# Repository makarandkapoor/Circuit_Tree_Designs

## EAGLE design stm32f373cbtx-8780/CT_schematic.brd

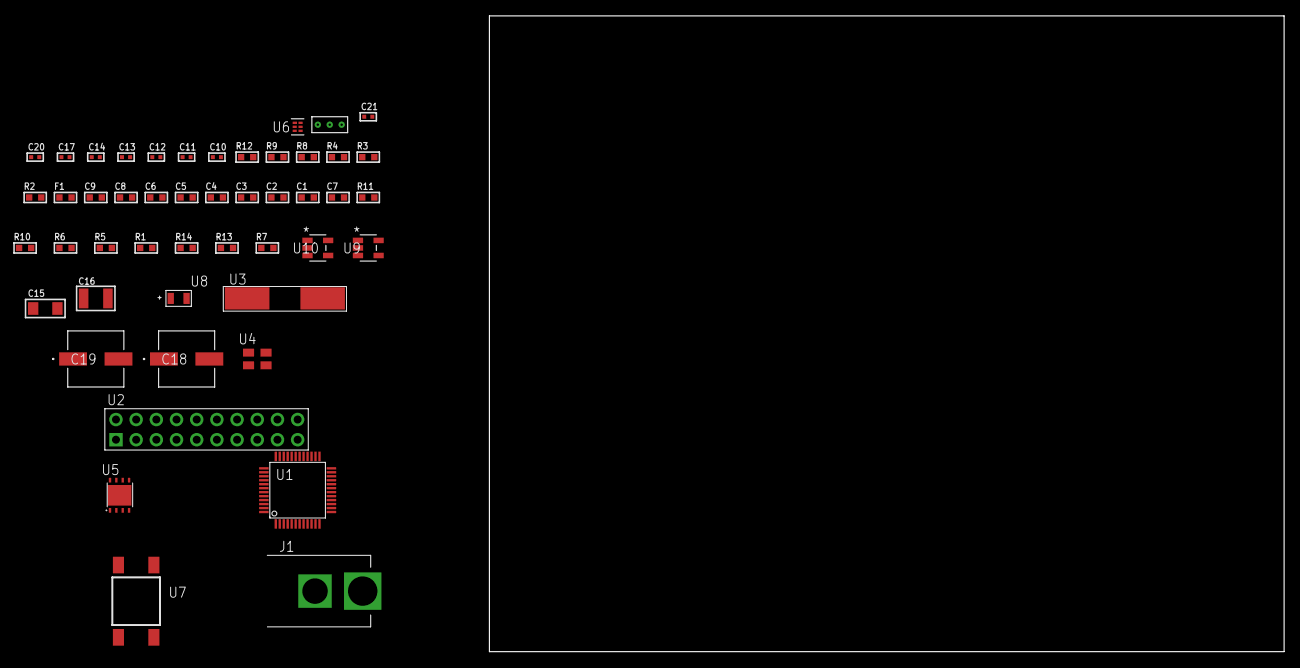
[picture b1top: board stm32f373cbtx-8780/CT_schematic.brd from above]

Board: 2 copper layers, 100.0 x 80.0 mm, 48 parts (0 on the bottom side), 24 nets, no tracks yet.

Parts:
C1, C9: 1e-06; C0603
C2, C3, C4, C5, C6: 1e-07; C0603
C7: 4.7e-06; C0603
C8: 1e-08; C0603
C10, C11: 1e-11; C0402
C12, C17: 1e-07; C0402
C13, C14, C20, C21: 1e-08; C0402
C15: 1e-05; C1206
C16: 1e-05; C1210
C18, C19: 0.0001; EXV-9H
F1: 240.0; L0603
J1: PJ-037B; PJ-037B_PACKAGE
R1, R5, R6, R10, R11: 10000.0; R0603
R2, R9: 1000.0; R0603
R3: 1600.5; R0603
R4: 4700.0; R0603
R7: 100000.0; R0603
R8: 2231.0; R0603
R12: 9100.0; R0603
R13: 680000.0; R0603
R14: 120000.0; R0603
U1: STM32F373CBT7; LQFP48
U2: TST-110-05-T-D-RA
U3: ABLS-25.000MHZ-B2F-T
U4: ASEK-32.768KHz-ECST; ASEK
U5: LP3878SDX-ADJ/NOPB; WSON-8
U6: TPS3895ADRYR; SON-6
U7: 4-1437565-2; SW_4-1437565-2
U8: Q65110A2395; LGM67K-G1J2-24-Z
U9, U10: nc7sz125m5x; NC7SZ125M5X
U11: Dummy; DUMMY_PACKAGE_98

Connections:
CLK_CRYSTAL_U1_5: C10.1, U1.5, U3.1
CLK_CRYSTAL_U1_6: C11.1, U1.6, U3.2
CLK_U1_3: U1.3, U4.3
GND: C1.2, C2.2, C3.2, C4.2, C5.2, C6.2, C7.2, C8.2, C9.2, C10.2, C11.2, C12.2, C13.2, C14.2, C15.2, C16.2, C17.2, C18.2, C19.2, C20.2, C21.2, J1.2, R2.2, R5.2, R9.2, R12.2, R14.2, U1.8, U1.23, U1.47, U2.4, U2.6, U2.8, U2.10, U2.12, U2.14, U2.16, U2.18, U2.20, U4.2, U5.3, U5.PAD, U6.2, U8.C, U9.2, U9.3, U10.1, U10.3, U11.1
NET_U1_7: R4.1, U1.7, U10.4
NET_U1_9: C8.1, C9.1, F1.1, U1.9, U1.24, U1.25
NET_U1_44: R5.1, U1.44
NET_U1_45: R3.1, U1.45, U8.A
NET_U1_46: R1.1, U1.46, U7.3, U7.4
NET_U5_1: C14.1, U5.1
NET_U5_6: R8.2, R9.1, U5.6
NET_U5_8: R7.1, U5.8
NET_U6_1: R11.1, R12.1, U6.1
NET_U6_3: R13.2, R14.1, U6.3
NET_U6_4: R10.1, U6.4, U9.4, U10.2
NET_U7_1: R2.1, U7.1, U7.2
PROC_SYS_JTCK_SWCLK: U1.37, U2.9
PROC_SYS_JTDO_TRACESWO: U1.39, U2.13
PROC_SYS_JTMS_SWDIO: U1.34, U2.7
PROC_TIM12_CH1: U1.14, U11.3
PROC_TIM12_CH2: U1.15, U11.2
RST_OUT_U2_SRESET_B: R6.1, U2.15, U9.1
VCC_S1_5V9: C15.1, C18.1, C19.1, J1.1, R7.2, U5.4
VCC_TIER1_3V3: C1.1, C2.1, C3.1, C4.1, C5.1, C6.1, C7.1, C12.1, C13.1, C16.1, C17.1, C20.1, C21.1, F1.2, R1.2, R3.2, R4.2, R6.2, R8.1, R10.2, R11.2, R13.1, U1.1, U1.17, U1.48, U2.1, U4.4, U5.5, U6.6, U9.5, U10.5

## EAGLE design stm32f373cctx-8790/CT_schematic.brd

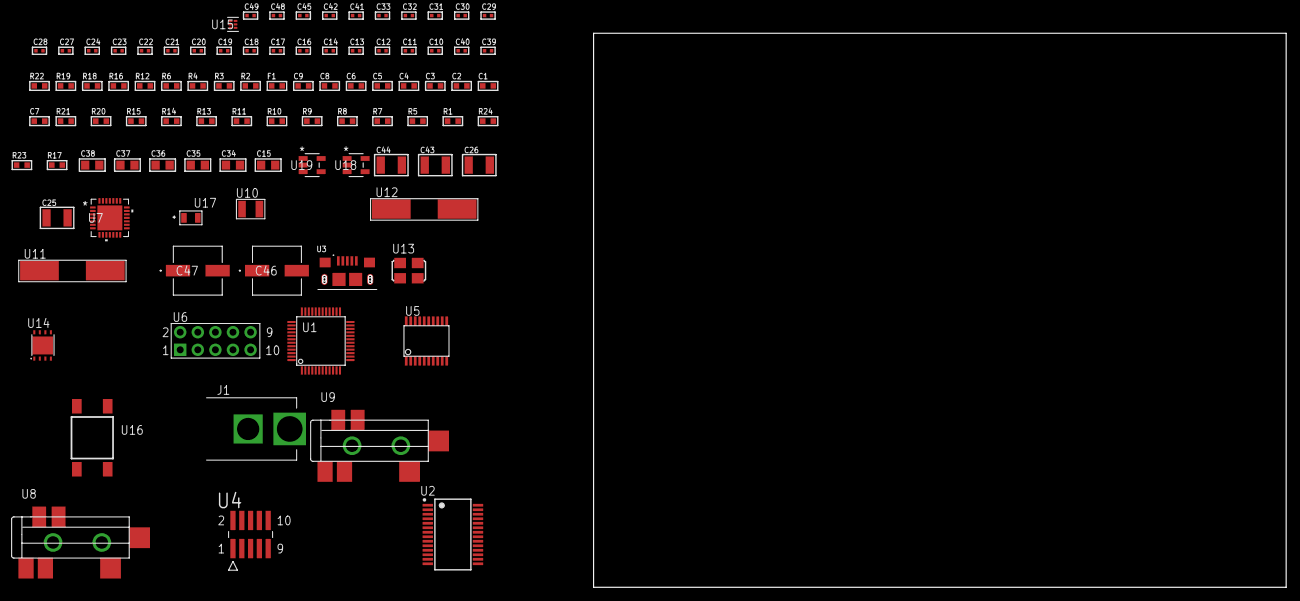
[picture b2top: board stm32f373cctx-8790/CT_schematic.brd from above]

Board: 2 copper layers, 94 parts (0 on the bottom side), 58 nets, no tracks yet.

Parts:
C1, C9: 1e-06; C0603
C2, C3, C4, C5, C6: 1e-07; C0603
C7: 4.7e-06; C0603
C8: 1e-08; C0603
C10, C11, C12, C13: 1e-11; C0402
C14, C16, C17, C18, C19, C20, C21, C22, C23, C24, C29, C30, C31, C32, C33, C45: 1e-07; C0402
C15: 4.7e-06; C0805
C25, C26: 2.2e-05; C1210
C27, C28: 1e-09; C0402
C34, C35, C36, C37, C38: 1e-05; C0805
C39, C40: 2.2e-11; C0402
C41, C42, C48, C49: 1e-08; C0402
C43, C44: 1e-05; C1210
C46, C47: 0.0001; EXV-9H
F1: 240.0; L0603
J1: PJ-037B; PJ-037B_PACKAGE
R1, R5, R7, R8, R9, R10, R11, R20, R21: 10000.0; R0603
R2, R19: 1000.0; R0603
R3: 1600.5; R0603
R4, R6: 4700.0; R0603
R12: 5.0; R0603
R13, R14, R15: 47000.0; R0603
R16: 680.0; R0603
R17: 100000.0; R0603
R18: 2231.0; R0603
R22: 9100.0; R0603
R23: 680000.0; R0603
R24: 120000.0; R0603
U1: STM32F373CCT6; LQFP48
U2: FT232RL-REEL; SSOP-28
U3: 10118193-0001LF; FCI_10118193-0001LF
U4: FTSH-105-01-L-DV-K; SAMTEC_FTSH-105-01-L-DV-K
U5: SP3203ECY-L/TR; TSSOP20-I
U6: HTSS-105-01-G-D
U7: WM8731CLSEFL; QFN-28
U8, U9: SJ-43515TS-SMT-TR
U10: ABS07-32.768KHZ-7-T
U11: ABLS-25.000MHZ-B2F-T
U12: ABLS-12.288MHZ-B4-T
U13: ASFL1-12MHZ-NCS; ASFL1
U14: LP3878SDX-ADJ/NOPB; WSON-8
U15: TPS3895ADRYR; SON-6
U16: 4-1437565-2; SW_4-1437565-2
U17: Q65110A2395; LGM67K-G1J2-24-Z
U18, U19: nc7sz125m5x; NC7SZ125M5X

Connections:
CLK_CRYSTAL_U1_3: C10.1, U1.3, U10.1
CLK_CRYSTAL_U1_4: C11.1, U1.4, U10.2
CLK_CRYSTAL_U1_5: C12.1, U1.5, U11.1
CLK_CRYSTAL_U1_6: C13.1, U1.6, U11.2
CLK_CRYSTAL_U7_1: C39.1, U7.1, U12.1
CLK_CRYSTAL_U7_2: C40.1, U7.2, U12.2
CLK_U2_27: U2.27, U13.3
GND: C1.2, C2.2, C3.2, C4.2, C5.2, C6.2, C7.2, C8.2, C9.2, C10.2, C11.2, C12.2, C13.2, C14.2, C15.2, C16.2, C17.2, C18.2, C19.2, C20.2, C23.2, C24.2, C28.2, C29.2, C30.2, C31.2, C32.2, C33.2, C34.2, C35.2, C36.2, C37.2, C38.2, C39.2, C40.2, C41.2, C42.2, C43.2, C44.2, C45.2, C46.2, C47.2, C48.2, C49.2, J1.2, R2.2, R5.2, R8.2, R12.2, R13.2, R14.2, R15.2, R19.2, R22.2, R24.2, U1.8, U1.23, U1.47, U2.7, U2.18, U2.21, U2.25, U2.26, U3.5, U3.6, U3.7, U3.8, U3.9, U4.3, U4.5, U5.18, U6.9, U7.4, U7.15, U7.19, U7.25, U7.26, U7.29, U8.1, U9.1, U13.2, U14.3, U14.PAD, U15.2, U17.C, U18.2, U18.3, U19.1, U19.3
NET_U1_7: R4.1, U1.7, U19.4
NET_U1_9: C8.1, C9.1, F1.1, U1.9, U1.24, U1.25
NET_U1_44: R5.1, U1.44
NET_U1_45: R3.1, U1.45, U17.A
NET_U1_46: R1.1, U1.46, U16.3, U16.4
NET_U2_14: R7.1, U2.14
NET_U2_17: C16.1, U2.17
NET_U2_19: R8.1, U2.19
NET_U3_1: R6.1, U3.1
NET_U3_2: U2.16, U3.2
NET_U3_3: U2.15, U3.3
NET_U4_9: R12.1, U4.9
NET_U5_1: C21.1, U5.1
NET_U5_2: C23.1, U5.2
NET_U5_3: C21.2, U5.3
NET_U5_4: C22.1, U5.4
NET_U5_5: C22.2, U5.5
NET_U5_6: C24.1, U5.6
NET_U6_3: U5.14, U6.3
NET_U6_4: U5.13, U6.4
NET_U6_5: U5.17, U6.5
NET_U6_6: U5.16, U6.6
NET_U7_20: C33.1, C38.1, U7.20
NET_U8_2: C26.1, R14.1, U8.2
NET_U8_5: C25.1, R13.1, U8.5
NET_U9_5: C27.1, C28.1, R15.1, R16.1, U9.5
NET_U14_1: C42.1, U14.1
NET_U14_6: R18.2, R19.1, U14.6
NET_U14_8: R17.1, U14.8
NET_U15_1: R21.1, R22.1, U15.1
NET_U15_3: R23.2, R24.1, U15.3
NET_U15_4: R20.1, U15.4, U18.4, U19.2
NET_U16_1: R2.1, U16.1, U16.2
PROC_I2S1_CK: U1.15, U7.7
PROC_I2S1_SD: U1.18, U7.8
PROC_I2S1_WS: U1.14, U7.9, U7.11
PROC_SYS_JTCK_SWCLK: R10.1, U1.37, U4.4
PROC_SYS_JTDO_TRACESWO: U1.39, U4.6
PROC_SYS_JTMS_SWDIO: R11.1, U1.34, U4.2
PROC_USART1_CTS: U1.32, U5.8
PROC_USART1_RTS: U1.33, U5.10
PROC_USART1_RX: U1.31, U5.11
PROC_USART1_TX: U1.30, U5.7
PROC_USART2_CTS: U1.10, U2.3
PROC_USART2_RTS: U1.11, U2.11
PROC_USART2_RX: U1.13, U2.1
PROC_USART2_TX: U1.12, U2.5
RST_OUT_U4_JTAG_RST_B: R9.1, U4.10, U18.1
VCC_S1_12V7: C43.1, C46.1, C47.1, J1.1, R17.2, U14.4
VCC_TIER1_3V3: C1.1, C2.1, C3.1, C4.1, C5.1, C6.1, C7.1, C14.1, C15.1, C17.1, C18.1, C19.1, C20.1, C29.1, C30.1, C31.1, C32.1, C34.1, C35.1, C36.1, C37.1, C41.1, C44.1, C45.1, C48.1, C49.1, F1.2, R1.2, R3.2, R4.2, R7.2, R9.2, R10.2, R11.2, R18.1, R20.2, R21.2, R23.1, U1.1, U1.17, U1.48, U2.4, U2.20, U4.1, U5.12, U5.19, U7.3, U7.5, U7.12, U7.18, U13.4, U14.5, U15.6, U18.5, U19.5

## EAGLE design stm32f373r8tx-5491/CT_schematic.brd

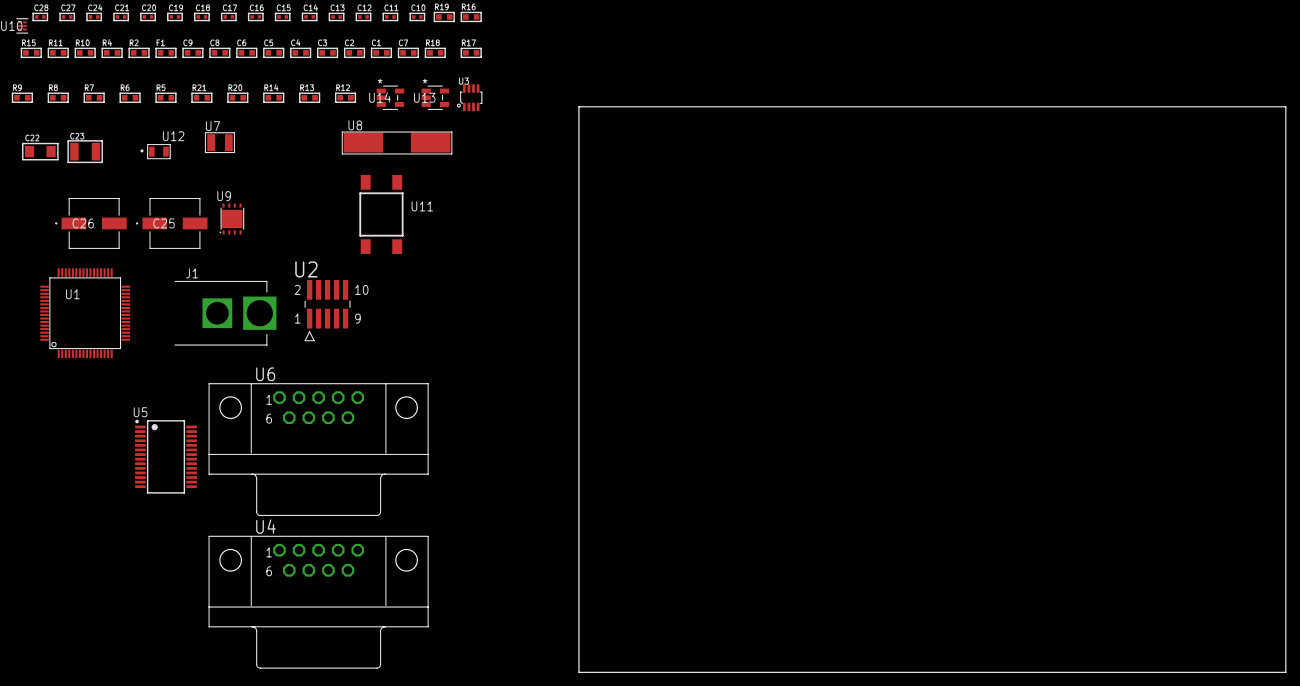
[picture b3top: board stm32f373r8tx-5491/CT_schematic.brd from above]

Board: 2 copper layers, 100.0 x 80.0 mm, 63 parts (0 on the bottom side), 45 nets, no tracks yet.

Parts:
C1, C9: 1e-06; C0603
C2, C3, C4, C5, C6: 1e-07; C0603
C7: 4.7e-06; C0603
C8: 1e-08; C0603
C10, C11, C12, C13: 1e-11; C0402
C14, C15, C16, C17, C18, C19, C20, C24: 1e-07; C0402
C21, C27, C28: 1e-08; C0402
C22: 1e-05; C1206
C23: 1e-05; C1210
C25, C26: 0.0001; EXV-9H
F1: 240.0; L0603
J1: PJ-037B; PJ-037B_PACKAGE
R2, R16: 1000.0; R0603
R4: 4700.0; R0603
R5, R6, R7, R8, R9, R17, R18: 10000.0; R0603
R10: 5.0; R0603
R11: 120.0; R0603
R12, R13, R14: 100000.0; R0603
R15: 2231.0; R0603
R19: 9100.0; R0603
R20: 680000.0; R0603
R21: 120000.0; R0603
U1: STM32F373R8T6; LQFP64
U2: FTSH-105-01-L-DV-K; SAMTEC_FTSH-105-01-L-DV-K
U3: MAX3051EKA+T; SOT-23-8
U4, U6: 182-009-113R531; 182-009-MALE
U5: ST3241EBPR; SSOP-28
U7: ABS07-32.768KHZ-7-T
U8: ABLS-25.000MHZ-B2F-T
U9: LP3878SDX-ADJ/NOPB; WSON-8
U10: TPS3895ADRYR; SON-6
U11: 4-1437565-2; SW_4-1437565-2
U12: Q65110A2395; LGM67K-G1J2-24-Z
U13, U14: nc7sz125m5x; NC7SZ125M5X

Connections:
CLK_CRYSTAL_U1_3: C10.1, U1.3, U7.1
CLK_CRYSTAL_U1_4: C11.1, U1.4, U7.2
CLK_CRYSTAL_U1_5: C12.1, U1.5, U8.1
CLK_CRYSTAL_U1_6: C13.1, U1.6, U8.2
GND: C1.2, C2.2, C3.2, C4.2, C5.2, C6.2, C7.2, C8.2, C9.2, C10.2, C11.2, C12.2, C13.2, C14.2, C15.2, C16.2, C19.2, C20.2, C21.2, C22.2, C23.2, C24.2, C25.2, C26.2, C27.2, C28.2, J1.2, R2.2, R5.2, R9.2, R10.2, R12.2, R16.2, R19.2, R21.2, U1.12, U1.31, U1.63, U2.3, U2.5, U3.2, U4.5, U5.23, U5.25, U6.5, U9.3, U9.PAD, U10.2, U12.C, U13.2, U13.3, U14.1, U14.3
NET_U1_7: R4.1, U1.7, U14.4
NET_U1_13: C8.1, C9.1, F1.1, U1.13, U1.17, U1.32
NET_U1_59: U11.3, U11.4
NET_U1_60: R5.1, U1.60
NET_U2_9: R10.1, U2.9
NET_U3_6: R11.2, U3.6
NET_U3_8: R12.1, U3.8
NET_U4_2: R11.2, U3.6, U4.2
NET_U4_3: R11.1, U3.7, U4.3
NET_U5_1: C18.1, U5.1
NET_U5_2: C18.2, U5.2
NET_U5_3: C20.1, U5.3
NET_U5_22: R13.1, U5.22
NET_U5_24: C17.2, U5.24
NET_U5_27: C19.1, U5.27
NET_U5_28: C17.1, U5.28
NET_U6_2: U5.4, U6.2
NET_U6_3: U5.9, U6.3
NET_U6_7: U5.5, U6.7
NET_U6_8: U5.10, U6.8
NET_U9_1: C21.1, U9.1
NET_U9_6: R15.2, R16.1, U9.6
NET_U9_8: R14.1, U9.8
NET_U10_1: R18.1, R19.1, U10.1
NET_U10_3: R20.2, R21.1, U10.3
NET_U10_4: R17.1, U10.4, U13.4, U14.2
NET_U11_1: R2.1, U11.1, U11.2
PROC_CAN_RX: U1.61, U3.4
PROC_CAN_TX: U1.62, U3.1
PROC_SYS_JTCK_SWCLK: R9.1, U1.49, U2.4
PROC_SYS_JTDI: R7.1, U1.50, U2.8
PROC_SYS_JTDO_TRACESWO: U1.55, U2.6
PROC_SYS_JTMS_SWDIO: R8.1, U1.46, U2.2
PROC_USART1_CTS: U1.44, U5.13
PROC_USART1_RTS: U1.45, U5.18
PROC_USART1_RX: U1.25, U5.19
PROC_USART1_TX: U1.24, U5.14
RST_OUT_U2_JTAG_RST_B: R6.1, U2.10, U13.1
VCC_S1_10V7: C22.1, C25.1, C26.1, J1.1, R14.2, U9.4
VCC_TIER1_3V3: C1.1, C2.1, C3.1, C4.1, C5.1, C6.1, C7.1, C14.1, C15.1, C16.1, C23.1, C24.1, C27.1, C28.1, F1.2, R4.2, R6.2, R7.2, R8.2, R13.2, R15.1, R17.2, R18.2, R20.1, U1.1, U1.19, U1.64, U2.1, U3.3, U5.26, U9.5, U10.6, U13.5, U14.5

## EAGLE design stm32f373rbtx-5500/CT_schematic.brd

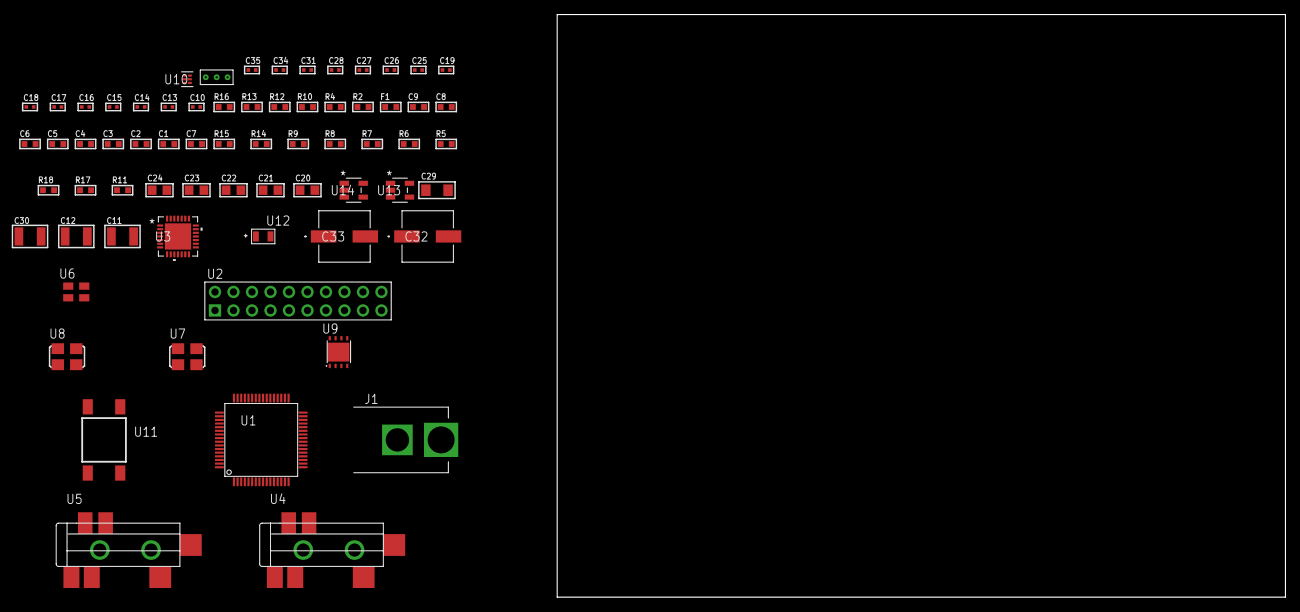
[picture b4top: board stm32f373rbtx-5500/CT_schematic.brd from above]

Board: 2 copper layers, 100.0 x 80.0 mm, 68 parts (0 on the bottom side), 30 nets, no tracks yet.

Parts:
C1, C9: 1e-06; C0603
C2, C3, C4, C5, C6: 1e-07; C0603
C7: 4.7e-06; C0603
C8: 1e-08; C0603
C10, C15, C16, C17, C18, C19, C31: 1e-07; C0402
C11, C12: 2.2e-05; C1210
C13, C14: 1e-09; C0402
C20, C21, C22, C23, C24: 1e-05; C0805
C25, C26, C27, C28, C34, C35: 1e-08; C0402
C29: 1e-05; C1206
C30: 1e-05; C1210
C32, C33: 0.0001; EXV-9H
F1: 240.0; L0603
J1: PJ-037B; PJ-037B_PACKAGE
R2, R13: 1000.0; R0603
R4: 4700.0; R0603
R5, R6, R14, R15: 10000.0; R0603
R7, R8, R9: 47000.0; R0603
R10: 680.0; R0603
R11: 100000.0; R0603
R12: 2231.0; R0603
R16: 9100.0; R0603
R17: 680000.0; R0603
R18: 120000.0; R0603
U1: STM32F373RBT6; LQFP64
U2: TST-110-05-T-D-RA
U3: WM8731CLSEFL; QFN-28
U4, U5: SJ-43515TS-SMT-TR
U6: ASEK-32.768KHz-ECST; ASEK
U7: ASFL1-12.288MHZ-EC-T; ASFL1
U8: ASFL1-25MHZ-NCS; ASFL1
U9: LP3878SDX-ADJ/NOPB; WSON-8
U10: TPS3895ADRYR; SON-6
U11: 4-1437565-2; SW_4-1437565-2
U12: Q65110A2395; LGM67K-G1J2-24-Z
U13, U14: nc7sz125m5x; NC7SZ125M5X
U15: Dummy; DUMMY_PACKAGE_145

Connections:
CLK_U1_3: U1.3, U6.3
CLK_U1_5: U1.5, U8.3
CLK_U3_1: U3.1, U7.3
GND: C1.2, C2.2, C3.2, C4.2, C5.2, C6.2, C7.2, C8.2, C9.2, C10.2, C14.2, C15.2, C16.2, C17.2, C18.2, C19.2, C20.2, C21.2, C22.2, C23.2, C24.2, C25.2, C26.2, C27.2, C28.2, C29.2, C30.2, C31.2, C32.2, C33.2, C34.2, C35.2, J1.2, R2.2, R5.2, R7.2, R8.2, R9.2, R13.2, R16.2, R18.2, U1.12, U1.31, U1.63, U2.4, U2.6, U2.8, U2.10, U2.12, U2.14, U2.16, U2.18, U2.20, U3.4, U3.15, U3.19, U3.25, U3.26, U3.29, U4.1, U5.1, U6.2, U7.2, U8.2, U9.3, U9.PAD, U10.2, U12.C, U13.2, U13.3, U14.1, U14.3, U15.1
NET_U1_7: R4.1, U1.7, U14.4
NET_U1_13: C8.1, C9.1, F1.1, U1.13, U1.17
NET_U1_60: R5.1, U1.60
NET_U1_62: U11.3, U11.4
NET_U3_20: C19.1, C24.1, U3.20
NET_U4_2: C12.1, R8.1, U4.2
NET_U4_5: C11.1, R7.1, U4.5
NET_U5_5: C13.1, C14.1, R9.1, R10.1, U5.5
NET_U9_1: C28.1, U9.1
NET_U9_6: R12.2, R13.1, U9.6
NET_U9_8: R11.1, U9.8
NET_U10_1: R15.1, R16.1, U10.1
NET_U10_3: R17.2, R18.1, U10.3
NET_U10_4: R14.1, U10.4, U13.4, U14.2
NET_U11_1: R2.1, U11.1, U11.2
PROC_ADC1_IN1: U1.15, U15.3
PROC_ADC1_IN2: U1.16, U15.2
PROC_I2S1_CK: U1.21, U3.7
PROC_I2S1_SD: U1.23, U3.8
PROC_I2S1_WS: U1.20, U3.9, U3.11
PROC_SYS_JTCK_SWCLK: U1.49, U2.9
PROC_SYS_JTDO_TRACESWO: U1.55, U2.13
PROC_SYS_JTMS_SWDIO: U1.46, U2.7
RST_OUT_U2_SRESET_B: R6.1, U2.15, U13.1
VCC_S1_6V3: C29.1, C32.1, C33.1, J1.1, R11.2, U9.4
VCC_TIER1_3V3: C1.1, C2.1, C3.1, C4.1, C5.1, C6.1, C7.1, C10.1, C15.1, C16.1, C17.1, C18.1, C20.1, C21.1, C22.1, C23.1, C25.1, C26.1, C27.1, C30.1, C31.1, C34.1, C35.1, F1.2, R4.2, R6.2, R12.1, R14.2, R15.2, R17.1, U1.1, U1.19, U1.64, U2.1, U3.3, U3.5, U3.12, U3.18, U6.4, U7.4, U8.4, U9.5, U10.6, U13.5, U14.5

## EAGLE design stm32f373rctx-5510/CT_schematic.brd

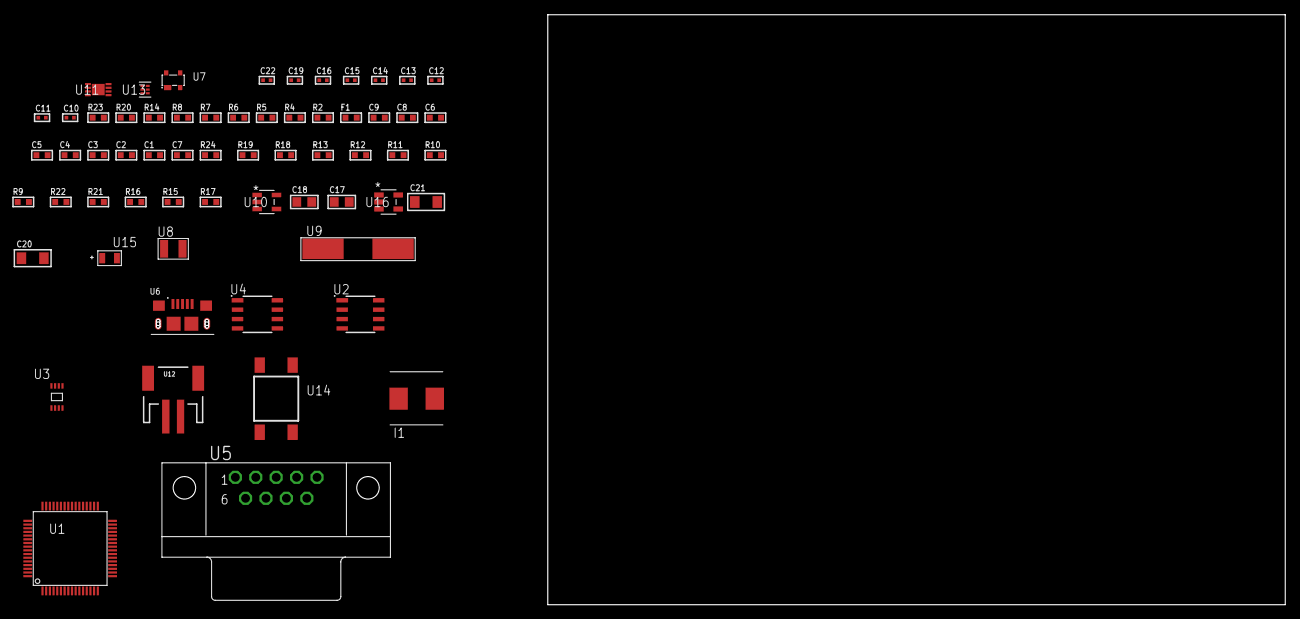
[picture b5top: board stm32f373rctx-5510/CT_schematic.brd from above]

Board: 2 copper layers, 62 parts (0 on the bottom side), 37 nets, no tracks yet.

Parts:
C1, C9: 1e-06; C0603
C2, C3, C4, C5, C6: 1e-07; C0603
C7: 4.7e-06; C0603
C8: 1e-08; C0603
C10, C11, C12, C13: 1e-11; C0402
C14, C15, C22: 1e-08; C0402
C16, C19: 1e-07; C0402
C17, C18: 1e-05; C0805
C20, C21: 1e-05; C1206
F1: 240.0; L0603
I1: 2e-06; WE-HCI_7030/7040/7050
R2: 1000.0; R0603
R4: 4700.0; R0603
R5, R6, R7, R8: 2200.0; R0603
R9, R10, R11, R12, R13, R18, R19, R24: 10000.0; R0603
R14: 120.0; R0603
R15: 100000.0; R0603
R16: 220000.0; R0603
R17: 1000000.0; R0603
R20: 9100.0; R0603
R21: 680000.0; R0603
R22: 120000.0; R0603
R23: 2000.0; R0603
U1: STM32F373RCT6; LQFP64
U2: AT24C02D-SSHM-T; AT24C02D
U3: 24AA08T-I/MNY; TDFN-8/6MM
U4: SN65HVD230D; SOIC-8
U5: 182-009-113R531; 182-009-MALE
U6: 10118193-0001LF; FCI_10118193-0001LF
U7: prtr5v0u2ax; SOT143B
U8: ABS07-32.768KHZ-7-T
U9: ABLS-25.000MHZ-B2F-T
U10: ltc3406es5; TSOT-23-5
U11: MCP73831T-2ACI/MC; DFN8_2X3MC
U12: S2B-PH-SM4-TB(LF)(SN); JST-2-SMD
U13: TPS3895ADRYR; SON-6
U14: 4-1437565-2; SW_4-1437565-2
U15: Q65110A2395; LGM67K-G1J2-24-Z
U16: nc7sz125m5x; NC7SZ125M5X

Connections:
CLK_CRYSTAL_U1_3: C10.1, U1.3, U8.1
CLK_CRYSTAL_U1_4: C11.1, U1.4, U8.2
CLK_CRYSTAL_U1_5: C12.1, U1.5, U9.1
CLK_CRYSTAL_U1_6: C13.1, U1.6, U9.2
GND: C1.2, C2.2, C3.2, C4.2, C5.2, C6.2, C7.2, C8.2, C9.2, C10.2, C11.2, C12.2, C13.2, C14.2, C15.2, C16.2, C17.2, C18.1, C18.2, C19.2, C20.2, C21.2, C22.2, R2.2, R9.2, R10.2, R12.2, R13.2, R15.2, R16.2, R20.2, R22.2, R23.2, U1.12, U1.31, U1.63, U2.4, U3.4, U4.2, U5.5, U6.5, U6.6, U6.7, U6.8, U6.9, U7.1, U10.2, U11.6, U11.9, U12.2, U13.2, U15.C, U16.1, U16.3
INPUT_USBPOWER_5V: C20.1, R24.2, U6.1, U7.4, U11.1, U11.2
NET_U1_7: R4.1, U1.7, U16.4
NET_U1_13: C8.1, C9.1, F1.1, U1.13, U1.17, U1.32
NET_U1_42: R7.1, U1.42, U3.6
NET_U1_43: R8.1, U1.43, U3.5
NET_U1_49: R6.1, U1.49, U2.5
NET_U1_50: R5.1, U1.50, U2.6
NET_U1_59: U14.3, U14.4
NET_U1_60: R9.1, U1.60
NET_U2_1: R11.1, U2.1
NET_U2_2: R12.1, U2.2
NET_U2_3: R13.1, U2.3
NET_U2_7: R10.1, U2.7
NET_U4_6: R14.2, U4.6
NET_U4_8: R15.1, U4.8
NET_U5_2: R14.2, U4.6, U5.2
NET_U5_3: R14.1, U4.7, U5.3
NET_U10_3: I1.1, U10.3
NET_U10_5: R16.1, R17.1, U10.5
NET_U10_ATNET_3: I1.2, R17.2
NET_U11_5: R24.1, U11.5
NET_U11_8: R23.1, U11.8
NET_U13_1: R19.1, R20.1, U13.1
NET_U13_3: R21.2, R22.1, U13.3
NET_U13_4: R18.1, U13.4, U16.2
NET_U14_1: R2.1, U14.1, U14.2
PROC_CAN_RX: U1.61, U4.4
PROC_CAN_TX: U1.62, U4.1
PROC_USB_DM: U1.44, U6.2, U7.3
PROC_USB_DP: U1.45, U6.3, U7.2
VCC_S1_3V7: C17.1, C21.1, U10.4, U11.3, U11.4, U12.1
VCC_TIER1_3V3: C1.1, C2.1, C3.1, C4.1, C5.1, C6.1, C7.1, C14.1, C15.1, C16.1, C18.2, C19.1, C22.1, F1.2, I1.2, R4.2, R5.2, R6.2, R7.2, R8.2, R11.2, R17.2, R18.2, R19.2, R21.1, U1.1, U1.19, U1.64, U2.8, U3.7, U3.8, U4.3, U13.6, U16.5

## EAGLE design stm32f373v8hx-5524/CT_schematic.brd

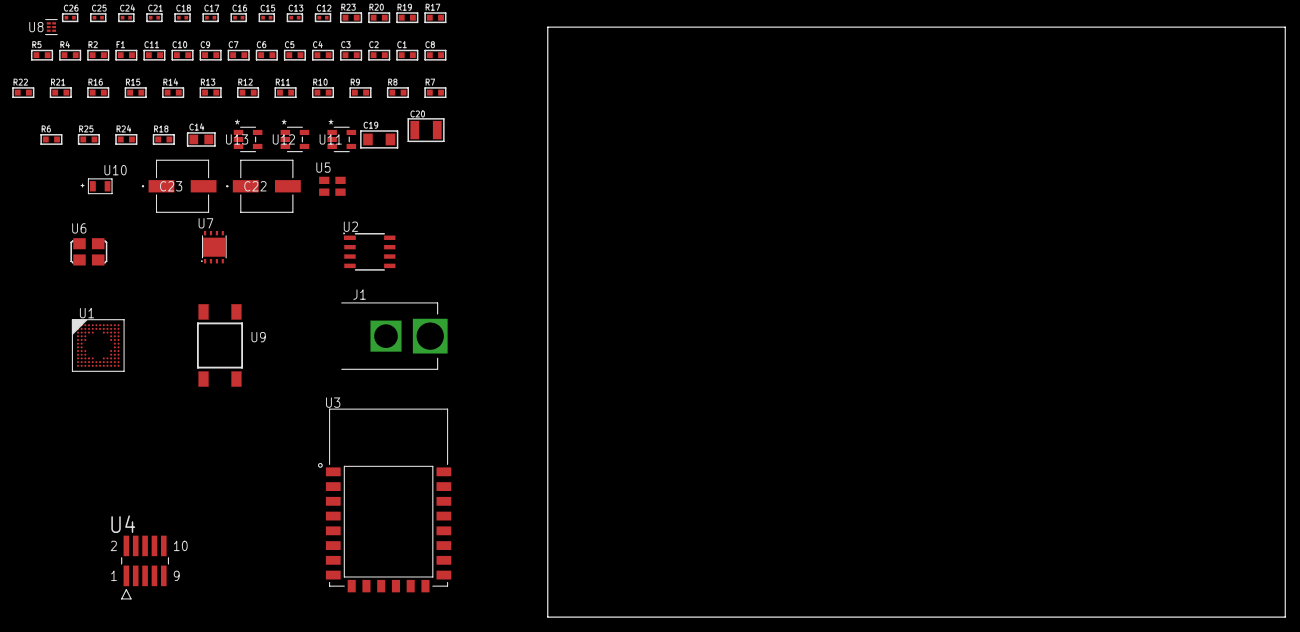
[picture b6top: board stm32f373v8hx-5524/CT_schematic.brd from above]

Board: 2 copper layers, 100.0 x 80.0 mm, 64 parts (0 on the bottom side), 36 nets, no tracks yet.

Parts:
C1, C11: 1e-06; C0603
C2, C3, C4, C5, C6, C7, C9: 1e-07; C0603
C8: 4.7e-06; C0603
C10: 1e-08; C0603
C12, C16, C17, C18, C24, C25, C26: 1e-08; C0402
C13, C15, C21: 1e-07; C0402
C14: 1e-05; C0805
C19: 1e-05; C1206
C20: 1e-05; C1210
C22, C23: 0.0001; EXV-9H
F1: 240.0; L0603
J1: PJ-037B; PJ-037B_PACKAGE
R2, R20: 1000.0; R0603
R4, R5: 4700.0; R0603
R6, R7, R8, R9, R10, R11, R12, R13, R14, R15, R16, R21, R22: 10000.0; R0603
R17: 5.0; R0603
R18: 100000.0; R0603
R19: 2231.0; R0603
R23: 9100.0; R0603
R24: 680000.0; R0603
R25: 120000.0; R0603
U1: STM32F373V8H6; UFBGA100
U2: AT25010B-SSHL-T; SOIC-8
U3: ESP8266-12E
U4: FTSH-105-01-L-DV-K; SAMTEC_FTSH-105-01-L-DV-K
U5: ASEK-32.768KHz-ECST; ASEK
U6: ASFL1-25MHZ-NCS; ASFL1
U7: LP3878SDX-ADJ/NOPB; WSON-8
U8: TPS3895ADRYR; SON-6
U9: 4-1437565-2; SW_4-1437565-2
U10: Q65110A2395; LGM67K-G1J2-24-Z
U11, U12, U13: nc7sz125m5x; NC7SZ125M5X

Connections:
CLK_U1_D1: U1.D1, U5.3
CLK_U1_F1: U1.F1, U6.3
GND: C1.2, C2.2, C3.2, C4.2, C5.2, C6.2, C7.2, C8.2, C9.2, C10.2, C11.2, C12.2, C13.2, C14.2, C15.2, C16.2, C17.2, C18.2, C19.2, C20.2, C21.2, C22.2, C23.2, C24.2, C25.2, C26.2, J1.2, R2.2, R6.2, R12.2, R16.2, R17.2, R20.2, R23.2, R25.2, U1.D3, U1.F11, U1.K1, U2.4, U3.15, U4.3, U4.5, U5.2, U6.2, U7.3, U7.PAD, U8.2, U10.C, U11.2, U11.3, U12.1, U12.3, U13.1, U13.3
NET_U1_A4: R6.1, U1.A4
NET_U1_F12: C9.1, U1.F12, U1.L11
NET_U1_H2: R5.1, U1.H2, U13.4
NET_U1_M1: C10.1, C11.1, F1.1, U1.G12, U1.L1, U1.L12, U1.M1
NET_U1_M12: U9.3, U9.4
NET_U2_3: R7.1, U2.3
NET_U2_7: R9.1, U2.7
NET_U3_1: R4.1, U3.1, U12.4
NET_U3_3: R10.1, U3.3
NET_U3_18: R11.1, U3.18
NET_U4_9: R17.1, U4.9
NET_U7_1: C18.1, U7.1
NET_U7_6: R19.2, R20.1, U7.6
NET_U7_8: R18.1, U7.8
NET_U8_1: R22.1, R23.1, U8.1
NET_U8_3: R24.2, R25.1, U8.3
NET_U8_4: R21.1, U8.4, U11.4, U12.2, U13.2
NET_U9_1: R2.1, U9.1, U9.2
PROC_SPI1_MISO: U1.A7, U3.6
PROC_SPI1_MOSI: U1.C5, U3.7
PROC_SPI1_NSS: R12.1, U1.B12, U3.16
PROC_SPI1_SCK: U1.A12, U3.5
PROC_SPI2_MISO: U1.B8, U2.2
PROC_SPI2_MOSI: U1.B7, U2.5
PROC_SPI2_NSS: R8.1, U1.B3, U2.1
PROC_SPI2_SCK: U1.A3, U2.6
PROC_SYS_JTCK_SWCLK: R16.1, U1.A10, U4.4
PROC_SYS_JTDI: R14.1, U1.A9, U4.8
PROC_SYS_JTDO_TRACESWO: U1.A8, U4.6
PROC_SYS_JTMS_SWDIO: R15.1, U1.A11, U4.2
RST_OUT_U4_JTAG_RST_B: R13.1, U4.10, U11.1
VCC_S1_10V0: C19.1, C22.1, C23.1, J1.1, R18.2, U7.4
VCC_TIER1_3V3: C1.1, C2.1, C3.1, C4.1, C5.1, C6.1, C7.1, C8.1, C12.1, C13.1, C14.1, C15.1, C16.1, C17.1, C20.1, C21.1, C24.1, C25.1, C26.1, F1.2, R4.2, R5.2, R7.2, R8.2, R9.2, R10.2, R11.2, R13.2, R14.2, R15.2, R19.1, R21.2, R22.2, R24.1, U1.C4, U1.E2, U1.G11, U1.H3, U2.8, U3.8, U4.1, U5.4, U6.4, U7.5, U8.6, U11.5, U12.5, U13.5

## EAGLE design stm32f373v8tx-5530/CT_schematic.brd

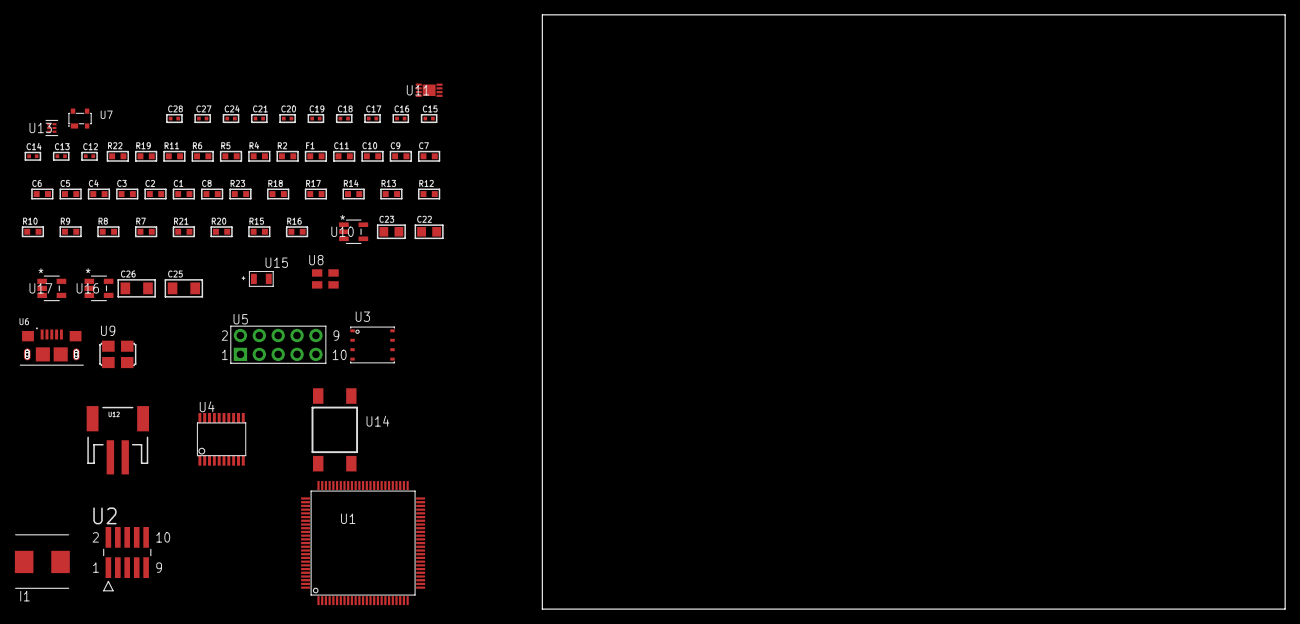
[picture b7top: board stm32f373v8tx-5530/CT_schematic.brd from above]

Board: 2 copper layers, 169.6 x 80.0 mm, 68 parts (0 on the bottom side), 46 nets, no tracks yet.

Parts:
C1, C11: 1e-06; C0603
C2, C3, C4, C5, C6, C7, C9: 1e-07; C0603
C8: 4.7e-06; C0603
C10: 1e-08; C0603
C12, C14, C15, C16, C17, C18, C19, C24: 1e-07; C0402
C13, C20, C21, C27, C28: 1e-08; C0402
C22, C23: 1e-05; C0805
C25, C26: 1e-05; C1206
F1: 240.0; L0603
I1: 2e-06; WE-HCI_7030/7040/7050
R2: 1000.0; R0603
R4: 4700.0; R0603
R5, R6: 2200.0; R0603
R7, R8, R9, R10, R12, R13, R14, R17, R18, R23: 10000.0; R0603
R11: 5.0; R0603
R15: 220000.0; R0603
R16: 1000000.0; R0603
R19: 9100.0; R0603
R20: 680000.0; R0603
R21: 120000.0; R0603
R22: 2000.0; R0603
U1: STM32F373V8T6; LQFP100
U2: FTSH-105-01-L-DV-K; SAMTEC_FTSH-105-01-L-DV-K
U3: 24AA512-I/MF; DFN8-S
U4: SP3203ECY-L/TR; TSSOP20-I
U5: HTSS-105-01-G-D
U6: 10118193-0001LF; FCI_10118193-0001LF
U7: prtr5v0u2ax; SOT143B
U8: ASEK-32.768KHz-ECST; ASEK
U9: ASFL1-25MHZ-NCS; ASFL1
U10: ltc3406es5; TSOT-23-5
U11: MCP73831T-2ACI/MC; DFN8_2X3MC
U12: S2B-PH-SM4-TB(LF)(SN); JST-2-SMD
U13: TPS3895ADRYR; SON-6
U14: 4-1437565-2; SW_4-1437565-2
U15: Q65110A2395; LGM67K-G1J2-24-Z
U16, U17: nc7sz125m5x; NC7SZ125M5X

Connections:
CLK_U1_8: U1.8, U8.3
CLK_U1_12: U1.12, U9.3
GND: C1.2, C2.2, C3.2, C4.2, C5.2, C6.2, C7.2, C8.2, C9.2, C10.2, C11.2, C12.2, C13.2, C14.2, C15.2, C18.2, C19.2, C20.2, C21.2, C22.2, C23.1, C23.2, C24.2, C25.2, C26.2, C27.2, C28.2, R2.2, R7.2, R11.2, R12.2, R14.2, R15.2, R19.2, R21.2, R22.2, U1.20, U1.74, U1.99, U2.3, U2.5, U3.4, U4.18, U5.9, U6.5, U6.6, U6.7, U6.8, U6.9, U7.1, U8.2, U9.2, U10.2, U11.6, U11.9, U12.2, U13.2, U15.C, U16.2, U16.3, U17.1, U17.3
INPUT_USBPOWER_5V: C25.1, R23.2, U6.1, U7.4, U11.1, U11.2
NET_U1_14: R4.1, U1.14, U17.4
NET_U1_21: C10.1, C11.1, F1.1, U1.21, U1.22, U1.50, U1.51
NET_U1_49: C9.1, U1.48, U1.49
NET_U1_77: R5.1, U1.77, U3.6
NET_U1_93: R6.1, U1.93, U3.5
NET_U1_94: R7.1, U1.94
NET_U1_98: U14.3, U14.4
NET_U2_9: R11.1, U2.9
NET_U3_1: R12.1, U3.1
NET_U3_2: R13.1, U3.2
NET_U3_3: R14.1, U3.3
NET_U4_1: C16.1, U4.1
NET_U4_2: C18.1, U4.2
NET_U4_3: C16.2, U4.3
NET_U4_4: C17.1, U4.4
NET_U4_5: C17.2, U4.5
NET_U4_6: C19.1, U4.6
NET_U5_3: U4.14, U5.3
NET_U5_4: U4.13, U5.4
NET_U5_5: U4.17, U5.5
NET_U5_6: U4.16, U5.6
NET_U10_3: I1.1, U10.3
NET_U10_5: R15.1, R16.1, U10.5
NET_U10_ATNET_3: I1.2, R16.2
NET_U11_5: R23.1, U11.5
NET_U11_8: R22.1, U11.8
NET_U13_1: R18.1, R19.1, U13.1
NET_U13_3: R20.2, R21.1, U13.3
NET_U13_4: R17.1, U13.4, U16.4, U17.2
NET_U14_1: R2.1, U14.1, U14.2
PROC_SYS_JTCK_SWCLK: R9.1, U1.76, U2.4
PROC_SYS_JTDO_TRACESWO: U1.89, U2.6
PROC_SYS_JTMS_SWDIO: R10.1, U1.72, U2.2
PROC_USART2_CTS: U1.23, U4.8
PROC_USART2_RTS: U1.24, U4.10
PROC_USART2_RX: U1.26, U4.11
PROC_USART2_TX: U1.25, U4.7
PROC_USB_DM: U1.70, U6.2, U7.3
PROC_USB_DP: U1.71, U6.3, U7.2
RST_OUT_U2_JTAG_RST_B: R8.1, U2.10, U16.1
VCC_S1_3V7: C22.1, C26.1, U10.4, U11.3, U11.4, U12.1
VCC_TIER1_3V3: C1.1, C2.1, C3.1, C4.1, C5.1, C6.1, C7.1, C8.1, C12.1, C13.1, C14.1, C15.1, C20.1, C21.1, C23.2, C24.1, C27.1, C28.1, F1.2, I1.2, R4.2, R5.2, R6.2, R8.2, R9.2, R10.2, R13.2, R16.2, R17.2, R18.2, R20.1, U1.6, U1.28, U1.75, U1.100, U2.1, U3.7, U3.8, U4.12, U4.19, U8.4, U9.4, U13.6, U16.5, U17.5

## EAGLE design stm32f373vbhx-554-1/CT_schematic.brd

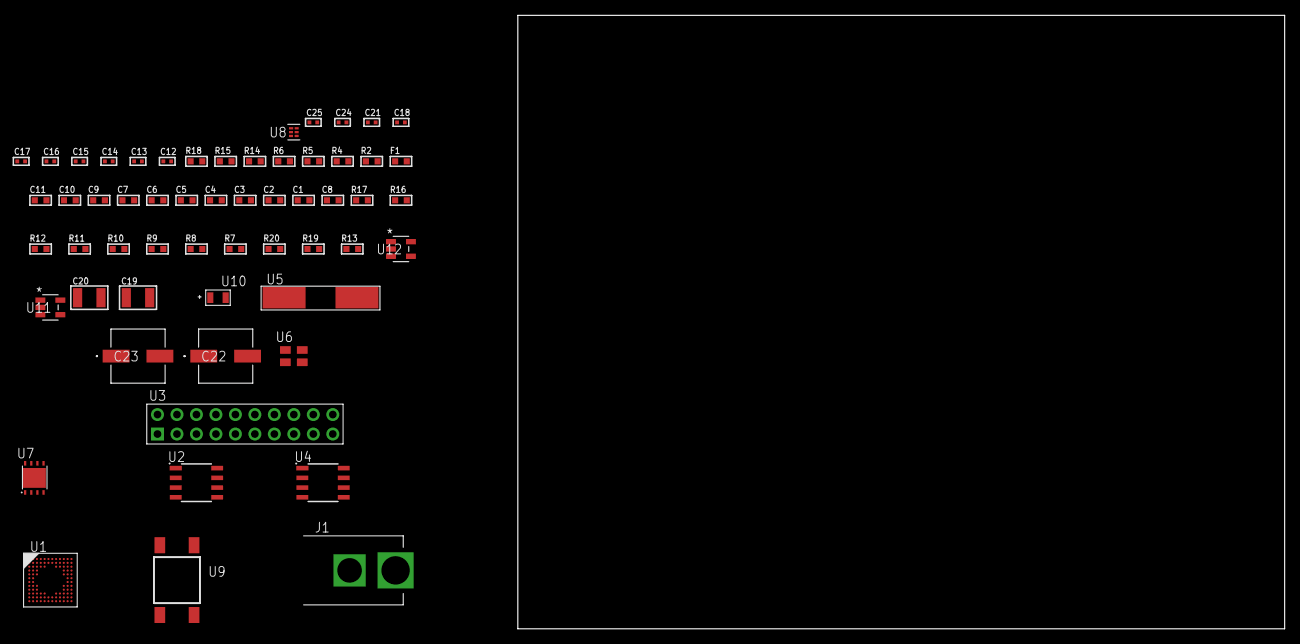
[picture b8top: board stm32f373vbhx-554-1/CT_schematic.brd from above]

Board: 2 copper layers, 100.0 x 80.0 mm, 57 parts (0 on the bottom side), 31 nets, no tracks yet.

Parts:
C1, C11: 1e-06; C0603
C2, C3, C4, C5, C6, C7, C9: 1e-07; C0603
C8: 4.7e-06; C0603
C10: 1e-08; C0603
C12, C13: 1e-11; C0402
C14, C16, C17, C18, C24, C25: 1e-08; C0402
C15, C21: 1e-07; C0402
C19, C20: 1e-05; C1210
C22, C23: 0.0001; EXV-9H
F1: 240.0; L0603
J1: PJ-037B; PJ-037B_PACKAGE
R2, R15: 1000.0; R0603
R4: 4700.0; R0603
R5, R6: 2200.0; R0603
R7, R8, R9, R10, R11, R12, R16, R17: 10000.0; R0603
R13: 100000.0; R0603
R14: 2231.0; R0603
R18: 9100.0; R0603
R19: 680000.0; R0603
R20: 120000.0; R0603
U1: STM32F373VBH6; UFBGA100
U2: AT25M01-SSHM-T; SOIC-8
U3: TST-110-05-T-D-RA
U4: M24M02-DRMN6TP; SOIC-8
U5: ABLS-25.000MHZ-B2F-T
U6: ASEK-32.768KHz-ECST; ASEK
U7: LP3878SDX-ADJ/NOPB; WSON-8
U8: TPS3895ADRYR; SON-6
U9: 4-1437565-2; SW_4-1437565-2
U10: Q65110A2395; LGM67K-G1J2-24-Z
U11, U12: nc7sz125m5x; NC7SZ125M5X

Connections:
CLK_CRYSTAL_U1_F1: C12.1, U1.F1, U5.1
CLK_CRYSTAL_U1_G1: C13.1, U1.G1, U5.2
CLK_U1_D1: U1.D1, U6.3
GND: C1.2, C2.2, C3.2, C4.2, C5.2, C6.2, C7.2, C8.2, C9.2, C10.2, C11.2, C12.2, C13.2, C14.2, C15.2, C16.2, C17.2, C18.2, C19.2, C20.2, C21.2, C22.2, C23.2, C24.2, C25.2, J1.2, R2.2, R7.2, R12.2, R15.2, R18.2, R20.2, U1.D3, U1.F11, U1.K1, U2.4, U3.4, U3.6, U3.8, U3.10, U3.12, U3.14, U3.16, U3.18, U3.20, U4.4, U6.2, U7.3, U7.PAD, U8.2, U10.C, U11.2, U11.3, U12.1, U12.3
NET_U1_A3: R5.1, U1.A3, U4.6
NET_U1_A4: R7.1, U1.A4
NET_U1_B3: R6.1, U1.B3, U4.5
NET_U1_F12: C9.1, U1.F12, U1.L11
NET_U1_H2: R4.1, U1.H2, U12.4
NET_U1_M1: C10.1, C11.1, F1.1, U1.G12, U1.L1, U1.L12, U1.M1
NET_U1_M12: U9.3, U9.4
NET_U2_3: R8.1, U2.3
NET_U2_7: R10.1, U2.7
NET_U4_3: R12.1, U4.3
NET_U7_1: C18.1, U7.1
NET_U7_6: R14.2, R15.1, U7.6
NET_U7_8: R13.1, U7.8
NET_U8_1: R17.1, R18.1, U8.1
NET_U8_3: R19.2, R20.1, U8.3
NET_U8_4: R16.1, U8.4, U11.4, U12.2
NET_U9_1: R2.1, U9.1, U9.2
PROC_SPI1_MISO: U1.A7, U2.2
PROC_SPI1_MOSI: U1.C5, U2.5
PROC_SPI1_NSS: R9.1, U1.A9, U2.1
PROC_SPI1_SCK: U1.A12, U2.6
PROC_SYS_JTCK_SWCLK: U1.A10, U3.9
PROC_SYS_JTDO_TRACESWO: U1.A8, U3.13
PROC_SYS_JTMS_SWDIO: U1.A11, U3.7
RST_OUT_U3_SRESET_B: R11.1, U3.15, U11.1
VCC_S1_14V7: C19.1, C22.1, C23.1, J1.1, R13.2, U7.4
VCC_TIER1_3V3: C1.1, C2.1, C3.1, C4.1, C5.1, C6.1, C7.1, C8.1, C14.1, C15.1, C16.1, C17.1, C20.1, C21.1, C24.1, C25.1, F1.2, R4.2, R5.2, R6.2, R8.2, R9.2, R10.2, R11.2, R14.1, R16.2, R17.2, R19.1, U1.C4, U1.E2, U1.G11, U1.H3, U2.8, U3.1, U4.8, U6.4, U7.5, U8.6, U11.5, U12.5
